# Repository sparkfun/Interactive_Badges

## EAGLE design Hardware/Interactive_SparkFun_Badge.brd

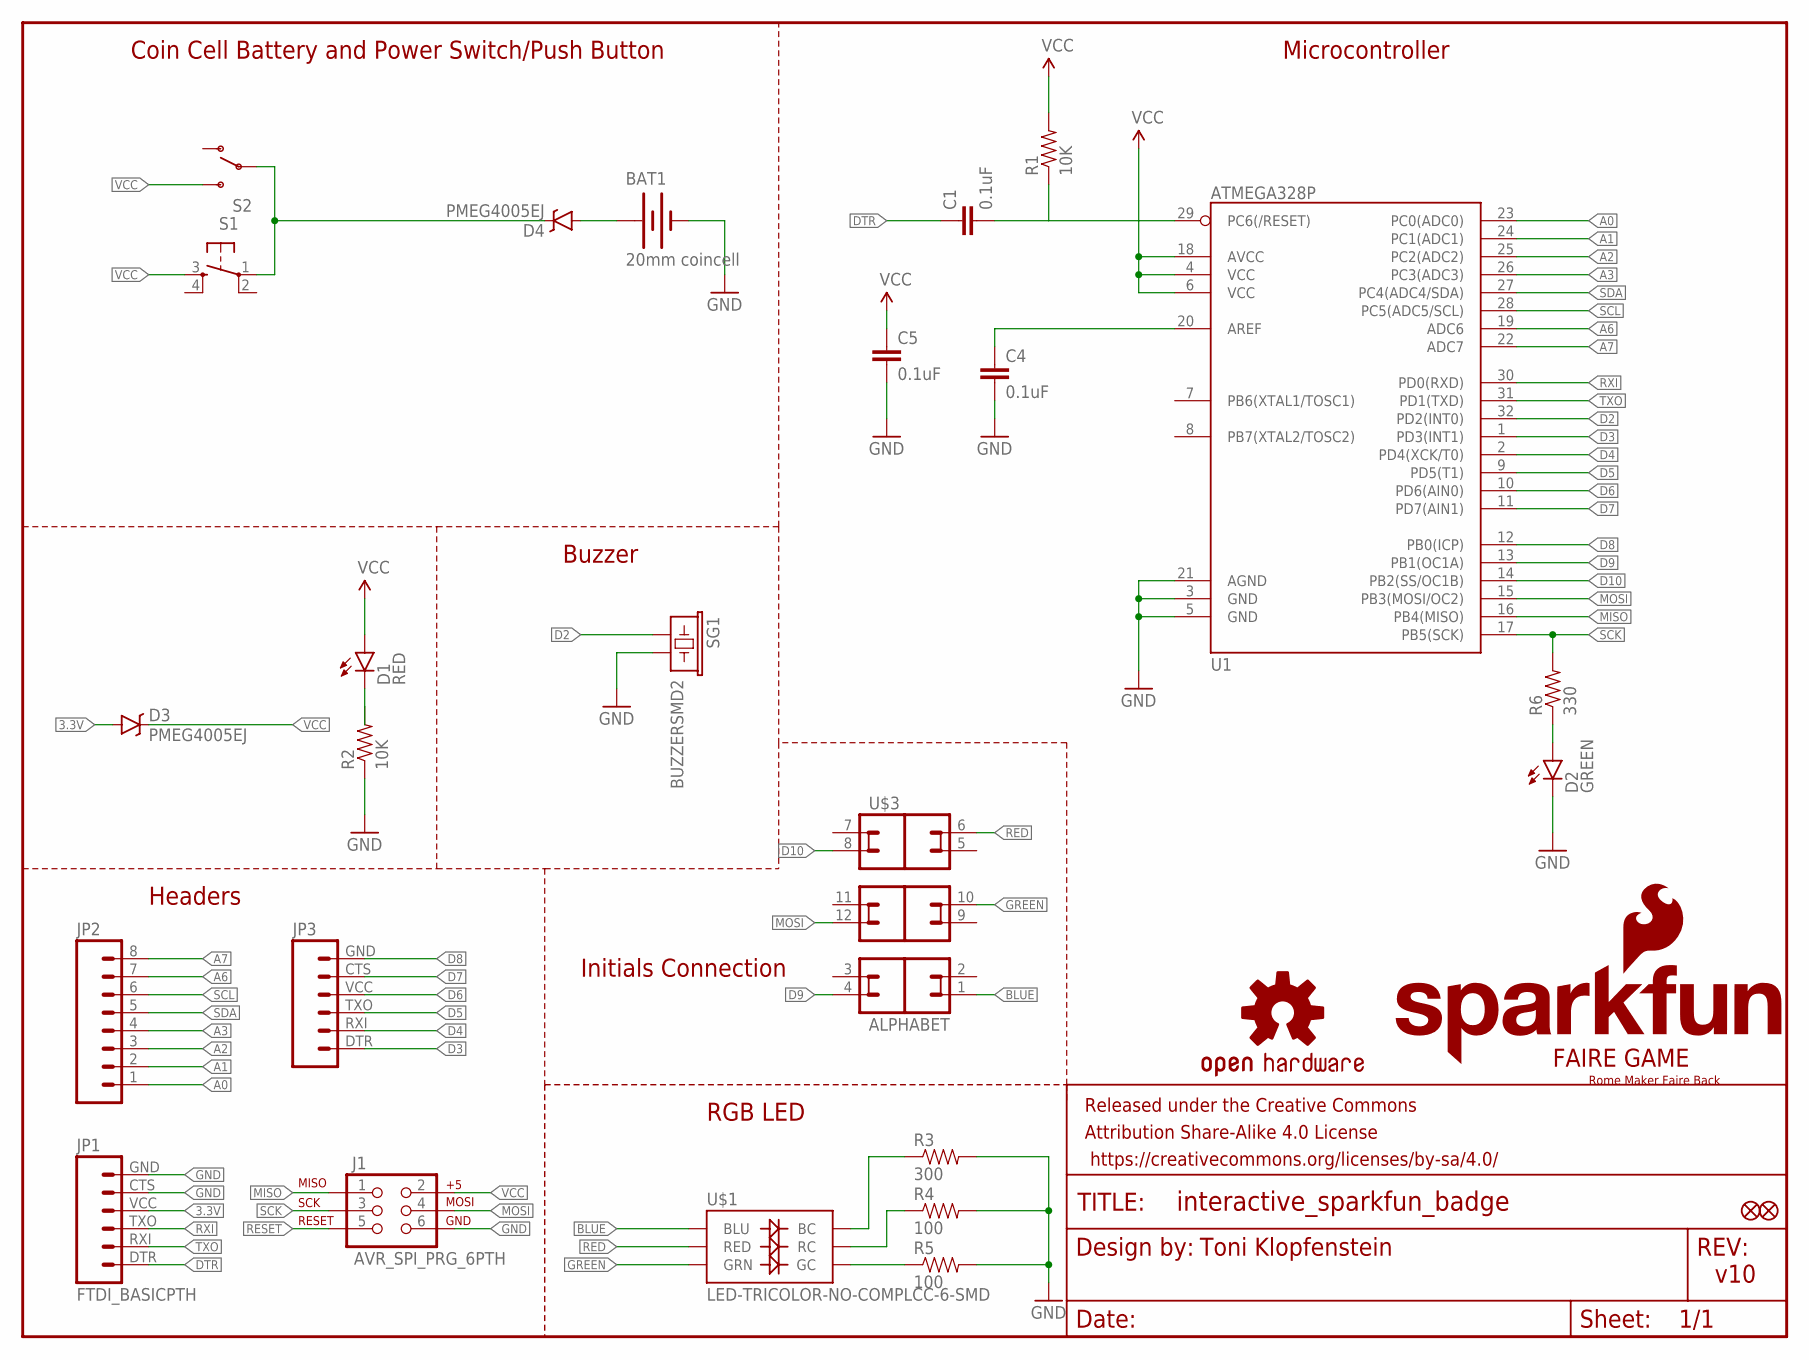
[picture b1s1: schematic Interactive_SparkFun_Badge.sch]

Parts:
BAT1: 20mm coincell; BATTCON_20MM_4LEGS
C1, C4, C5: 0.1uF; 0603-CAP
D1: RED; LED-0603
D2: GREEN; LED-0603
D3, D4: PMEG4005EJ; SOD-323
FID1, FID2: FIDUCIAL1X2; FIDUCIAL-1X2
FRAME1: FRAME-LETTER; CREATIVE_COMMONS
J1: AVR_SPI_PRG_6PTH; 2X3
JP1: FTDI_BASICPTH; FTDI_BASIC
JP2: M081X08; 1X08
JP3: M06SIP; 1X06
LOGO1: OSHW-LOGOM; OSHW-LOGO-M
R1, R2: 10K; 0603-RES
R3: 300; 0603-RES
R4, R5: 100; 0603-RES
R6: 330; 0603-RES
S1: TAC_SWITCHSMD; TACTILE-SWITCH-SMD
S2: SWITCH-SPDTSMD; AYZ0202
SG1: BUZZERSMD2; BUZZER-CCV
U1: ATMEGA328P; TQFP32-08
U$1: LED-TRICOLOR-NO-COMPLCC-6-SMD; PLCC-6-LED
U$2: ROME_FAIRE_BACK; ROME_BACK
U$3: ALPHABET; INITIALS
U$4: FAIRE_GAME_SILK

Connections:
3.3V: D3.A, JP1.VCC (4)
A0: JP2.1, U1.23 (PC0(ADC0))
A1: JP2.2, U1.24 (PC1(ADC1))
A2: JP2.3, U1.25 (PC2(ADC2))
A3: JP2.4, U1.26 (PC3(ADC3))
A6: JP2.7, U1.19 (ADC6)
A7: JP2.8, U1.22 (ADC7)
BLUE: U$1.AB (BLU), U$3.1
D2: SG1.+ (1), U1.32 (PD2(INT0))
D3: JP3.DTR (1), U1.1 (PD3(INT1))
D4: JP3.RXI (2), U1.2 (PD4(XCK/T0))
D5: JP3.TXO (3), U1.9 (PD5(T1))
D6: JP3.VCC (4), U1.10 (PD6(AIN0))
D7: JP3.CTS (5), U1.11 (PD7(AIN1))
D8: JP3.GND (6), U1.12 (PB0(ICP))
D9: U1.13 (PB1(OC1A)), U$3.4
D10: U1.14 (PB2(SS/OC1B)), U$3.8
DTR: C1.1, JP1.DTR (1)
GND: BAT1.2 (-), C4.2, C5.2, D2.C, J1.6, JP1.CTS (5), JP1.GND (6), R2.1, R3.2, R4.2, R5.2, SG1.- (2), U1.3 (GND), U1.5 (GND), U1.21 (AGND)
GREEN: U$1.AG (GRN), U$3.10
MISO: J1.1, U1.16 (PB4(MISO))
MOSI: J1.4, U1.15 (PB3(MOSI/OC2)), U$3.12
unnamed: D4.C, S1.1, S2.2
unnamed: R3.1, U$1.CB (BC)
unnamed: D1.C, R2.2
unnamed: R4.1, U$1.CR (RC)
unnamed: R5.1, U$1.CG (GC)
unnamed: C4.1, U1.20 (AREF)
unnamed: D2.A, R6.1
unnamed: BAT1.1 (+), D4.A
RED: U$1.AR (RED), U$3.6
RESET: C1.2, J1.5, R1.1, U1.29 (PC6(/RESET))
RXI: JP1.TXO (3), U1.30 (PD0(RXD))
SCK: J1.3, R6.2, U1.17 (PB5(SCK))
SCL: JP2.6, U1.28 (PC5(ADC5/SCL))
SDA: JP2.5, U1.27 (PC4(ADC4/SDA))
TXO: JP1.RXI (2), U1.31 (PD1(TXD))
VCC: C5.1, D1.A, D3.C, J1.2, R1.2, S1.3, S2.3 (S), U1.4 (VCC), U1.6 (VCC), U1.18 (AVCC)

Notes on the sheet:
v10
Toni Klopfenstein
RGB LED
Coin Cell Battery and Power Switch/Push Button
Buzzer
Microcontroller
Headers
Initials Connection

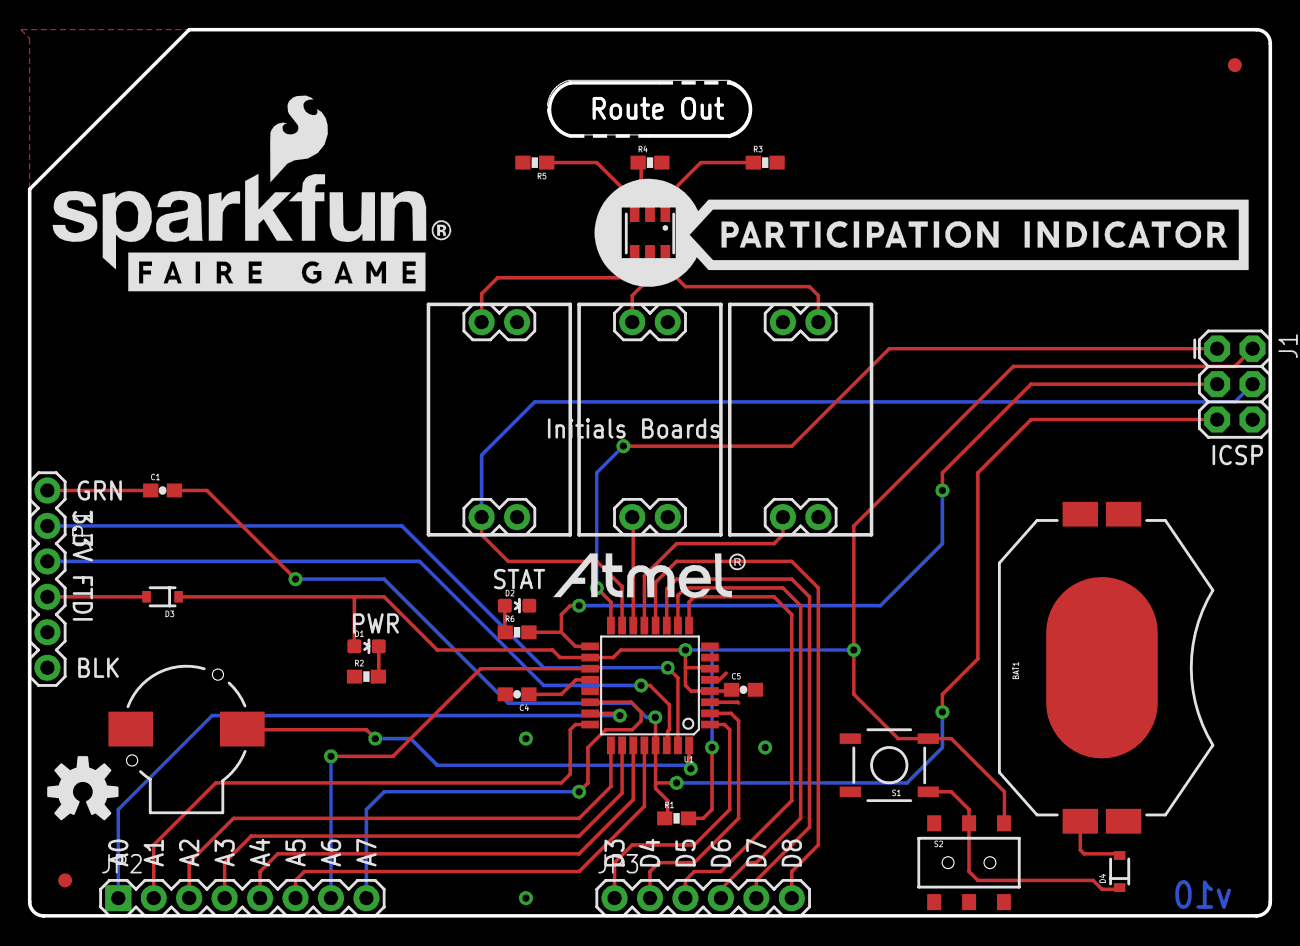
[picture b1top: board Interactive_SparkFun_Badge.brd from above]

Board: 2 copper layers, 88.9 x 63.5 mm, 30 parts (0 on the bottom side), 38 nets.

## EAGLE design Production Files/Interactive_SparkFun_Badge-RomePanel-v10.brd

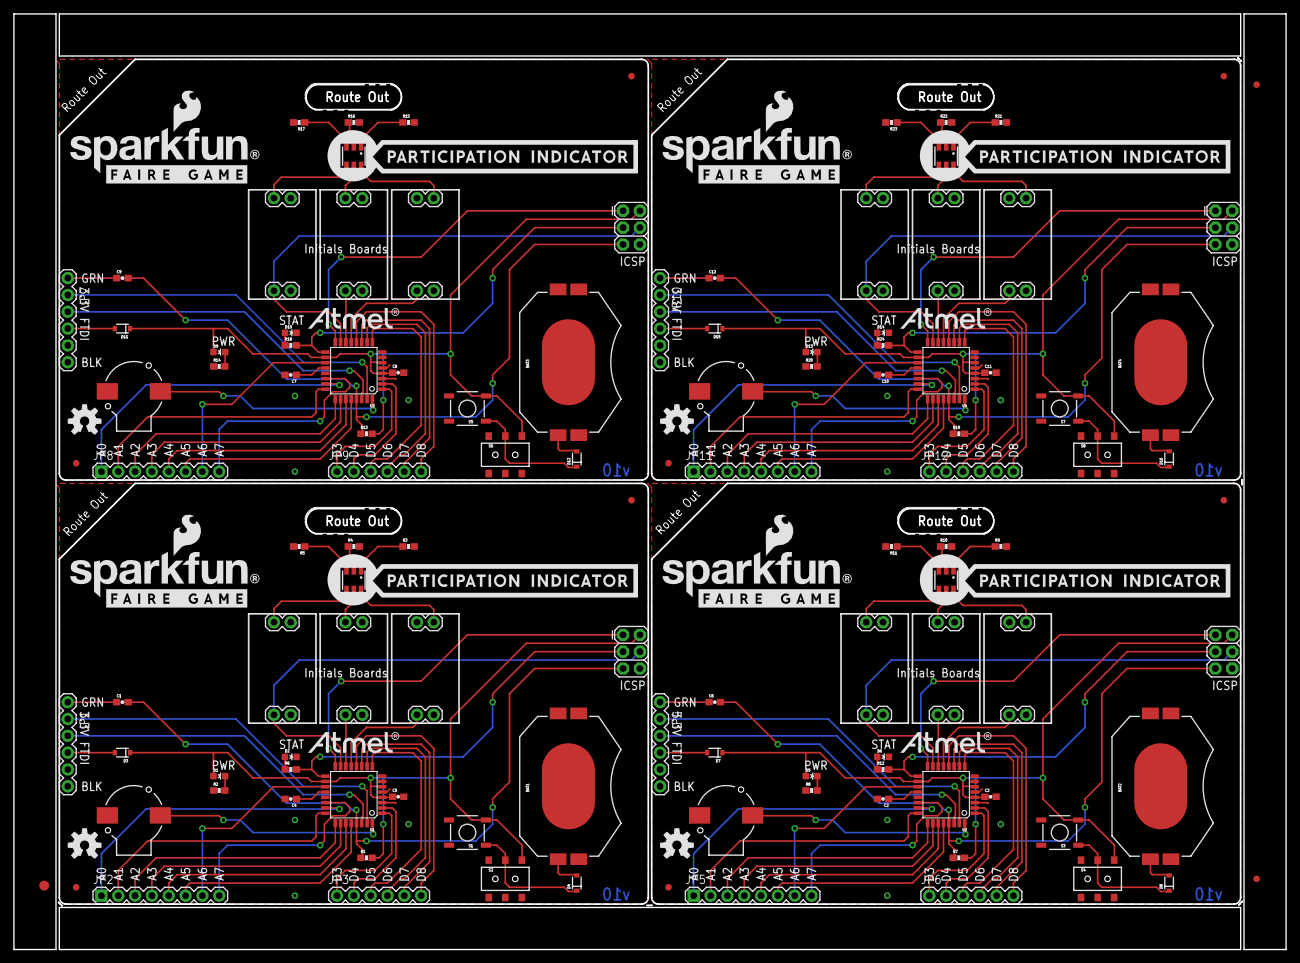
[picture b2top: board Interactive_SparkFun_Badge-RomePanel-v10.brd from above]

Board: 2 copper layers, 192.0 x 141.2 mm, 119 parts (0 on the bottom side), 152 nets.

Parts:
BAT1, BAT2, BAT3, BAT4: 20mm coincell; BATTCON_20MM_4LEGS
C1, C2, C3, C4, C5, C6, C7, C8, C9, C10, C11, C12: 0.1uF; 0603-CAP
D1, D5, D9, D13: RED; LED-0603
D2, D6, D10, D14: GREEN; LED-0603
D3, D4, D7, D8, D11, D12, D15, D16: DIODE-ZENER3.3V; SOD-323
E$1: FIDUCIAL-1.5X3
E$4, E$6: FIDUCIAL-1X2
FID1, FID2, FID3, FID4, FID5, FID6, FID7, FID8: FIDUCIAL1X2; FIDUCIAL-1X2
J1, J2, J3, J4: AVR_SPI_PRG_6PTH; 2X3
JP1, JP4, JP7, JP10: FTDI_BASICPTH; FTDI_BASIC
JP2, JP5, JP8, JP11: 1X08
JP3, JP6, JP9, JP12: 1X06
LOGO1, LOGO2, LOGO3, LOGO4: OSHW-LOGOM; OSHW-LOGO-M
R1, R2, R7, R8, R13, R14, R19, R20: 10K; 0603-RES
R3, R9, R15, R21: 300; 0603-RES
R4, R5, R10, R11, R16, R17, R22, R23: 100; 0603-RES
R6, R12, R18, R24: 330; 0603-RES
S1, S3, S5, S7: TACTILE-SWITCH-SMD
S2, S4, S6, S8: AYZ0202
SG1, SG2, SG3, SG4: BUZZERSMD2; BUZZER-CCV
U1, U2, U3, U4: ATMEGA328P; TQFP32-08
U$1, U$5, U$9, U$13: LED-TRICOLOR-NO-COMPLCC-6-SMD; PLCC-6-LED
U$2, U$8, U$12, U$16: ROME_FAIRE_BACK; ROME_BACK
U$3, U$6, U$10, U$14: ALPHABET; INITIALS
U$4, U$7, U$11, U$15: FAIRE_GAME_SILK

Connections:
3.3V: D3.A, JP1.VCC
3.3V1: D7.A, JP4.VCC
3.3V2: D11.A, JP7.VCC
3.3V3: D15.A, JP10.VCC
A0: JP2.1, U1.23
A1: JP2.2, U1.24
A2: JP2.3, U1.25
A3: JP2.4, U1.26
A4: JP5.1, U2.23
A5: JP5.2, U2.24
A6: JP2.7, U1.19
A7: JP2.8, U1.22
A8: JP5.3, U2.25
A9: JP5.4, U2.26
A10: JP5.7, U2.19
A11: JP5.8, U2.22
A12: JP8.1, U3.23
A13: JP8.2, U3.24
A14: JP8.3, U3.25
A15: JP8.4, U3.26
A16: JP8.7, U3.19
A17: JP8.8, U3.22
A18: JP11.1, U4.23
A19: JP11.2, U4.24
A20: JP11.3, U4.25
A21: JP11.4, U4.26
A22: JP11.7, U4.19
A23: JP11.8, U4.22
BLUE: U$1.AB, U$3.1
BLUE1: U$5.AB, U$6.1
BLUE2: U$9.AB, U$10.1
BLUE3: U$13.AB, U$14.1
D1: SG2.+, U2.32
D2: SG1.+, U1.32
D3: JP3.DTR, U1.1
D4: JP3.RXI, U1.2
D5: JP3.TXO, U1.9
D6: JP3.VCC, U1.10
D7: JP3.CTS, U1.11
D8: JP3.GND, U1.12
D9: U1.13, U$3.4
D10: U1.14, U$3.8
D11: JP6.DTR, U2.1
D12: JP6.RXI, U2.2
D13: JP6.TXO, U2.9
D14: JP6.VCC, U2.10
D15: JP6.CTS, U2.11
D16: JP6.GND, U2.12
D17: U2.13, U$6.4
D18: U2.14, U$6.8
D19: SG3.+, U3.32
D20: JP9.DTR, U3.1
D21: JP9.RXI, U3.2
D22: JP9.TXO, U3.9
D23: JP9.VCC, U3.10
D24: JP9.CTS, U3.11
D25: JP9.GND, U3.12
D26: U3.13, U$10.4
D27: U3.14, U$10.8
D28: SG4.+, U4.32
D29: JP12.DTR, U4.1
D30: JP12.RXI, U4.2
D31: JP12.TXO, U4.9
D32: JP12.VCC, U4.10
D33: JP12.CTS, U4.11
D34: JP12.GND, U4.12
D35: U4.13, U$14.4
D36: U4.14, U$14.8
DTR: C1.1, JP1.DTR
DTR1: C6.1, JP4.DTR
DTR2: C9.1, JP7.DTR
DTR3: C12.1, JP10.DTR
GND: BAT1.2, C4.2, C5.2, D2.C, J1.6, JP1.CTS, JP1.GND, R2.1, R3.2, R4.2, R5.2, SG1.-, U1.3, U1.5, U1.21
GND1: BAT2.2, C2.2, C3.2, D6.C, J2.6, JP4.CTS, JP4.GND, R8.1, R9.2, R10.2, R11.2, SG2.-, U2.3, U2.5, U2.21
GND2: BAT3.2, C7.2, C8.2, D10.C, J3.6, JP7.CTS, JP7.GND, R14.1, R15.2, R16.2, R17.2, SG3.-, U3.3, U3.5, U3.21
GND3: BAT4.2, C10.2, C11.2, D14.C, J4.6, JP10.CTS, JP10.GND, R20.1, R21.2, R22.2, R23.2, SG4.-, U4.3, U4.5, U4.21
GREEN: U$1.AG, U$3.10
GREEN1: U$5.AG, U$6.10
GREEN2: U$9.AG, U$10.10
GREEN3: U$13.AG, U$14.10
MISO: J1.1, U1.16
MISO1: J2.1, U2.16
MISO2: J3.1, U3.16
MISO3: J4.1, U4.16
MOSI: J1.4, U1.15, U$3.12
MOSI1: J2.4, U2.15, U$6.12
MOSI2: J3.4, U3.15, U$10.12
MOSI3: J4.4, U4.15, U$14.12
unnamed: D4.C, S1.1, S2.2
unnamed: C2.1, U2.20
unnamed: D5.C, R8.2
unnamed: R3.1, U$1.CB
unnamed: D1.C, R2.2
unnamed: R4.1, U$1.CR
unnamed: R5.1, U$1.CG
unnamed: C4.1, U1.20
unnamed: D2.A, R6.1
unnamed: BAT1.1, D4.A
unnamed: R9.1, U$5.CB
unnamed: R11.1, U$5.CG
unnamed: R10.1, U$5.CR
unnamed: D6.A, R12.1
unnamed: BAT2.1, D8.A
unnamed: D8.C, S3.1, S4.2
unnamed: C7.1, U3.20
unnamed: D9.C, R14.2
unnamed: R15.1, U$9.CB
unnamed: R17.1, U$9.CG
unnamed: R16.1, U$9.CR
unnamed: D10.A, R18.1
unnamed: BAT3.1, D12.A
unnamed: D12.C, S5.1, S6.2
unnamed: C10.1, U4.20
unnamed: D13.C, R20.2
unnamed: R21.1, U$13.CB
unnamed: R23.1, U$13.CG
unnamed: R22.1, U$13.CR
unnamed: D14.A, R24.1
unnamed: BAT4.1, D16.A
unnamed: D16.C, S7.1, S8.2
RED: U$1.AR, U$3.6
RED1: U$5.AR, U$6.6
RED2: U$9.AR, U$10.6
RED3: U$13.AR, U$14.6
RESET: C1.2, J1.5, R1.1, U1.29
RESET1: C6.2, J2.5, R7.1, U2.29
RESET2: C9.2, J3.5, R13.1, U3.29
RESET3: C12.2, J4.5, R19.1, U4.29
RXI: JP1.TXO, U1.30
RXI1: JP4.TXO, U2.30
RXI2: JP7.TXO, U3.30
RXI3: JP10.TXO, U4.30
SCK: J1.3, R6.2, U1.17
SCK1: J2.3, R12.2, U2.17
SCK2: J3.3, R18.2, U3.17
SCK3: J4.3, R24.2, U4.17
SCL: JP2.6, U1.28
SCL1: JP5.6, U2.28
SCL2: JP8.6, U3.28
SCL3: JP11.6, U4.28
SDA: JP2.5, U1.27
SDA1: JP5.5, U2.27
SDA2: JP8.5, U3.27
SDA3: JP11.5, U4.27
TXO: JP1.RXI, U1.31
TXO1: JP4.RXI, U2.31
TXO2: JP7.RXI, U3.31
TXO3: JP10.RXI, U4.31
VCC: C5.1, D1.A, D3.C, J1.2, R1.2, S1.3, S2.3, U1.4, U1.6, U1.18
VCC1: C3.1, D5.A, D7.C, J2.2, R7.2, S3.3, S4.3, U2.4, U2.6, U2.18
VCC2: C8.1, D9.A, D11.C, J3.2, R13.2, S5.3, S6.3, U3.4, U3.6, U3.18
VCC3: C11.1, D13.A, D15.C, J4.2, R19.2, S7.3, S8.3, U4.4, U4.6, U4.18

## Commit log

2014-08-07 Adding Rome MF back silk
2014-08-07 Fixing version number to v10
2014-08-08 created New York Panel v10
2014-08-08 Created Rome Panel v10
2014-09-02 Switching to Schottky diode

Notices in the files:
parts and their libraries:
SparkFun-Aesthetics: Licensing: Creative Commons ShareAlike 4.0 International - https://creativecommons.org/licenses/by-sa/4.0
SparkFun-Aesthetics: Released under the Creative Commons Attribution Share-Alike 4.0 License
SparkFun-Aesthetics: https://creativecommons.org/licenses/by-sa/4.0
